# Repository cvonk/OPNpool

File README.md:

> OPNpool moved to a ESPHome/PlatformIO based build system.  If you are looking for the last standalone version, you will find that in the `standalone` branch, or download the most recent `v1` release.

Ever dreamed of making your pool smarter and easier to manage? If you’ve ever owned a backyard pool, you know it’s not just about swimming—there’s a whole world of chemicals, covers, vacuums, brushes, and fiddling with thermostats and circuits. Even with a saltwater pool, you’ve got to keep a close eye on things!

Enter OPNpool: your pool’s new best friend. It takes all the classic pool controller features and brings them into your smart home. OPNpool keeps track of your controller, pump, and chlorinator, so you don’t have to run outside every time you want to check or change something. Even better, you can set up automations—like running the pump longer when it’s hot out—all from the comfort of your phone or smart home dashboard.

Thanks to some clever folks who reverse engineered the RS485 protocol, OPNpool can eavesdrop on the chatter between your pool’s components. The ESP32 inside shares all that state info with Home Assistant.

# OPNpool

OPNpool is an open-source hardware and software solution that brings advanced pool automation to your smart home. By bridging legacy pool controllers with modern IoT platforms, OPNpool enables real-time monitoring, remote control, and seamless integration with Home Assistant. Whether you want to automate your pool pump based on temperature, monitor chlorinator status, or simply enjoy the convenience of remote access, OPNpool provides a robust and extensible platform for pool management.

## How it works

At its core, OPNpool connects an ESP32 microcontroller to your pool controller’s RS-485 bus. The ESP32 runs ESPHome firmware, which translates pool equipment data into Home Assistant entities. This allows you to view and control your pool’s thermostats, pumps, circuits, and chlorinator directly from your smart home dashboard or mobile app. The system is designed for reliability, safety, and ease of installation, with support for over-the-air updates and waterproof enclosures for outdoor use.

## Features

- [x] **Smart Home Integration:** Native support for Home Assistant and ESPHome.
- [x] **Remote Monitoring & Control:** Access your pool’s status and controls from anywhere.
- [x] **Community Driven:** Built on the work of pool automation enthusiasts and reverse engineers.
- [x] **Open Source:** Fully transparent hardware and software—customize and extend as needed.

## Getting started

No prior experience with pool automation or ESPHome is required. The documentation below will guide you through hardware assembly, wiring, firmware installation, and Home Assistant integration. If you have questions or need help, join the project’s GitHub Discussions for community support.

This device was tested with the Pentair SunTouch controller with firmware **2.080** (2013-07-15), connected to an IntelliFlo pump and IntelliChlor saltwater chlorinator.

> This open source and hardware project is intended to comply with the October 2016 exemption to the Digital Millennium Copyright Act allowing "good-faith" testing," in a controlled environment designed to avoid any harm to individuals or to the public.

## Acknowledgements

> We proudly acknowledge the work of reverse engineering pioneers [Joshua Bloch](https://docs.google.com/document/d/1M0KMfXfvbszKeqzu6MUF_7yM6KDHk8cZ5nrH1_OUcAc/edit), [Michael Russe](http://cocoontech.com/forums/files/file/173-pab014sharezip/), and [George Saw](http://cocoontech.com/forums/topic/27864-download-pitzip/). (Drop me a line if I forgot you.)

## Usage

Start with [installing the ESPHome environment](https://esphome.io/guides/installing_esphome/) on a beefy computer. In my case, this cut the compilation time to a minute, compared to half an hour when running it as an add-on to Home Assistant.

In an empty directory, create a `opnpool-1.yaml` configuration file as shown below.
```yaml
substitutions:
  device_name: opnpool-1
  friendly_name: "OPNpool meets ESPHome"
  description: "External component, see https://github.com/cvonk/OPNpool_meets_ESPHome"

esphome:
  name: ${device_name}
  comment: ${description}
  friendly_name: ${friendly_name}

esp32:
  variant: esp32c6          # or esp32     for <= r3 boards
  board: esp32-c6-devkitc-1 # or lolin_d32 for <= r3 boards
  framework:
    type: esp-idf

wifi:
  domain: !secret domain_name # only needed if not on the same subnet
  min_auth_mode: WPA2
  reboot_timeout: 0s
  networks:
  - ssid: !secret wifi_ssid
    password: !secret wifi_password

api:

ota:
  - platform: esphome
    password: !secret ota_password

external_components:
  - source: github://cvonk/OPNpool
    components: [ opnpool ]

logger:
  level: VERBOSE          # build includes ESP_LOGx up to VERBOSE
  initial_level: WARN     # only show up to WARN globally
  logs:
    poolstate_rx: VERBOSE # show decoded messages

opnpool:
  id: opnpool_1
  RS-485:
    tx_pin:  21  # or 26 for <= r3 boards 
    rx_pin:  22  # or 25 for <= r3 boards
    rts_pin: 23  # or 27 for <= r3 boards
```

Specify your own secrets in `secrets.yaml`

```yaml
wifi_ssid: "REDACTED"
wifi_password: "REDACTED"
domain_name: ".iot.example.com" # appended to base fname to create FQDN for OTA updates
ota_password: "REDACTED"
api_encryption_key: "REDACTED"
```

Compile and upload the code using

```bash
esphome run opnpool-1.yaml
```

The first time, you need to upload over USB Serial, but after that you can use over-the-air updates.

In the output, you should see something like:

```text
[16:26:54.983]I (423) boot: Loaded app from partition at offset 0x10000
[16:26:55.024]I (465) boot: Set actual ota_seq=1 in otadata[0]
[16:26:55.029]I (465) boot: Disabling RNG early entropy source...
[16:26:55.268][W][component:333]: api set Warning flag: unspecified
[16:26:55.273][W][component:342]: wifi set Warning flag: scanning for networks
[16:27:01.293][W][component:373]: wifi cleared Warning flag
[16:27:25.143][E][RS-485:108][pool_req_task]: tx_q full
[16:27:55.144][E][RS-485:108][pool_req_task]: tx_q full
```

In the above trace, the `tx_q full` indicates that it can't transmit to the pool controller.

If you haven't already, add the ESPHome integration to Home Assistant.

Under Integrations, you will find now notice that Home Assistant auto discovered your new device.

{: style="display: block; margin-left: auto; margin-right: auto; width:300px;}

Add it, and specify your API key.  Name the device and assign it an area. You should then see the enities although their values are `unknown`.  Time to populate those entities by connecting it to the pool controller ;-)

## Connect

At the core this project is an ESP32 module and a 3.3 Volt RS-485 adapter. You can
breadboard this using:

* Any ESP32 module that has an USB connector and three GPIO pins available.
* Any "Max485 Module TTL". To make it 3.3 Volt compliant, change the chip to a `MAX3485CSA+`. While you're at it, you may as well remove the 10 kΩ pullup resistors (typically labeled `R1` to `R4`).
* A piece of Cat5 ethernet cable to connect to the pool controller.

{: style="display: block; margin-left: auto; margin-right: auto; width:300px;}

If you prefer to make this a more permanent solution, I suggest rolling a printed circuit board and housing it in a IP68 waterproof case with IP68 connectors.  More about this later.

> :warning: **THIS PROJECT IS OFFERED AS IS. IF YOU USE IT YOU ASSUME ALL RISKS. NO WARRANTIES. At the very least, turn off the power while you work on your pool equipment. Be careful, THERE IS ALWAYS A RISK OF BREAKING YOUR POOL EQUIPMENT.**

Understanding the above warning .. the RS-485 header can be found on the back of the control board. There are probably already wires connected that go to the devices such as pump and chlorinator.

{: style="display: block; margin-left: auto; margin-right: auto; width:400px;}

To minimize electromagnetic interference, use a twisted pairs from e.g. CAT-5 cable to connect the `A`/`B` pair to the RS-485 adapter as shown in the table below.

| Controller       | RS-485 adapter | idle state |         
|:-----------------|:--------------:|:-----------|
| `-DATA` (green)  |  `A`           | negative   |
| `+DATA` (yellow) |  `B`           | positive   |

Connect the RS-485 adapter to the ESP32 module.  I also pulled `GPIO#27` down with a 10 k&ohm; resistor, to keep it from transmiting while the ESP32 is booting.

| RS-485 adapter | ESP32 module |
|:---------------|:-------------|
| RO             | `GPIO#25`    |
| DI             | `GPIO#26`    |
| DE and RE      | `GPIO#27`    |
| GND            | `GND`        |

The serial monitor will start to show decoded messages such as:

```json
{CTRL_VERSION_REQ: {}}
{CTRL_VERSION_RESP: {"firmware":"2.80"}}
{CTRL_TIME_REQ: {}}
{CTRL_TIME_RESP: {"tod":{"time":"18:51","date":"2026-01-18"}}}
{CTRL_HEAT_REQ: {}}
{CTRL_HEAT_RESP: {"thermos":{"POOL":{"temp":54,"sp":63,"src":"NONE"},"SPA":{"temp":54,"sp"}
```

> :bulb: If you don't see such messages, make sure you didn't swap the data leads, or oddly enough some people report that they do need to swap the data leads.  To debug the datalink framing, set the `datalink_rx` logger level to `VERBOSE` and build and upload the code again. See futher below.

In Home Assistant the entities should populate, and show on your favorite Lovelace UI.

{: style="display: block; margin-left: auto; margin-right: auto; width:500px}

## PCB

For a robust and weatherproof installation, we recommend building a custom printed circuit board (PCB) to house the ESP32-C6 module, RS-485 adapter, and DC/DC converter. This approach ensures reliable connections, easier mounting, and long-term durability—especially for outdoor or poolside environments.

{: style="display: block; margin-left: auto; margin-right: auto; width:500px}

Note that the photo above is from a rev 1 board.

### Schematic

The hardware design features a buck converter that supplies 5V to the `5V0` pin on the ESP32-C6 DevKitC-1-N8 daughterboard. The scotty diode prevent issues when the board is also powered via USB.

The main data path runs between the RS-485 connector and the ESP32-C6 on the DevKitC-1-N8. An optional termination resistor is included to minimize signal reflections on the RS-485 bus.

### Board Layout

The entire schematic fits comfortably on a compact two-layer PCB. The board was designed using the free version of AutoDesk EAGLE, and all source files — including layout and schematics — are available in the [hardware directory](tree/main/hardware) of this repository.

{: style="display: block; margin-left: auto; margin-right: auto;}

### Bill of materials

| Name        | Description                                              | Suggested mfr/part#        | Price paid
|-------------|----------------------------------------------------------|----------------------------|-----------
| PBC r4      | Printed circuit board                                    | OSHPark                    | [$9.43](https://oshpark.com/)
| Enclosure   | 158x90x60mm ABS Plastic Junction Box, IP65               | *white label*              | [$9.81](https://www.harfington.com/products/p-1159792)
| RS-485_CONN | 5P Plug+socket, 5-pin, 16mm aviation, IP68               | SP16 5P                    | [$3.98](https://www.aliexpress.us/item/2251832722757291.html)
| RS-485-TERM | Fixed terminal block, 4-pin, screwless, 5 mm pitch       | Phoenix-Contact 1862437    | [$2.02](https://www.digikey.com/en/products/detail/phoenix-contact/1862437/6605421)
| ESP32-C6 DevKitC-1-N8 | ESP32-C6 dev board with 8MB flash, based on ESP32-C6-WROOM | ESP32-C6 DevKitC-1-N8      | [$9.00](https://www.digikey.com/en/products/detail/espressif-systems/ESP32-C6-DEVKITC-1-N8/17728861)
| MAX3485     | Maxim MAX3485CSA, RS-485/UART interface IC 3.3V, 8-SOIC  | Analog-Devices MAX3485CSA+T | [$5.64](https://www.digikey.com/en/products/detail/analog-devices-inc-maxim-integrated/MAX3485CSA-T/1703654)
| DC1         | DC/DC Converter R-78E5.0-0.5, 7-28V to 5V, 0.5A, 3-SIP   | RECOM-Power R-78E5.0-0.5   | [$3.30](https://www.digikey.com/en/products/detail/recom-power/R-78E5-0-0-5/2834904?s=N4IgTCBcDaIEoFEDCB5AsgWgAoHsDuApgE4AEcGA7ABwICsAdAAwaP20gC6AvkA)
| D1, D2      | Schottky Diode, 1N5818, 30V, 1A, DO-41                   | Diodes Incorporated 1N5818-T | [$0.30](https://www.digikey.com/en/products/detail/diodes-incorporated/1N5818-T/22054)
| LED1        | LED, Green Clear 571nm, 1206                             | Lite-On LTST-C150KGKT       | [$0.15](https://www.digikey.com/en/products/detail/liteon/LTST-C150KGKT/365085)
| LED2        | LED, Amber Clear 602nm, 1206                             | Lite-On LTST-C150AKT       | [$0.15](https://www.digikey.com/en/products/detail/liteon/LTST-C150AKT/269213)
| C1, C2      | Capacitor, 10 µF, 25 V, multi-layer ceramic, 0805        | KEMET C0805C106K3PACTU     | [$0.22](https://www.digikey.com/en/products/detail/kemet/C0805C106K3PACTU/5267604?s=N4IgTCBcDaINIFECyCAqACAwgBgBzYFZMBGbANjgGYAFAQU1QFUQBdAXyA)
| C3          | Capacitor, 100 nF, 25 V, multi-layer ceramic, 0805      | KEMET C0805C104M3RACTU     | [$0.12](https://www.digikey.com/en/products/detail/kemet/C0805C104M3RACTU/2211748?s=N4IgTCBcDaINIFECyCAqACAwgBgBzYFZMBGbAFiQGYAlAQU1QFUQBdAXyA)
| R1, R2      | Resistor, 68 Ω, 1/8 W, 0805                              | YAGEO RC0805FR-0768RL      | [$0.20](https://www.digikey.com/en/products/detail/yageo/RC0805FR-0768RL/728097?s=N4IgTCBcDaIJoEEDiBRA8gAgEoGEAMAHHgKwBiWAtHgOwBsBWAMiALoC%2BQA)
| R3          | Not stuffed, resistor, 120 Ω, 1/4 W, 0805                | KAO SG73S2ATTD121J         | [$0.00](https://www.digikey.com/en/products/detail/koa-speer-electronics-inc/RK73B2ATTD121J/10236600)
| PCB Screws  | Machine screw, #6-32 x x 3/16", panhead                  | Keystone-Electronics 9306  | [$0.10](https://www.digikey.com/en/products/detail/keystone-electronics/9306/2746085?s=N4IgjCBcpgTB0QGMoDMCGAbAzgUwDQgD2UA2iLAAwCsIAuoQA4AuUIAyswE4CWAdgHMQAX2GFYZEAGlcAT2zMifXAFoAoplxJuSnkmwACAJwBmSgDZ6woA)
| CONN Screws | Machine screw, M2-0.4 x 16 mm, cheese head               | Essentra 50M020040D016     | [$0.28](https://www.digikey.com/en/products/detail/essentra-components/50M020040D016/11639297)
| CONN Nuts   | Hex nut, M2-0.4, nylon                                   | Essentra 04M020040HN       | [$0.15](https://www.digikey.com/en/products/detail/essentra-components/04M020040HN/9677098)

Note that tariffs and shipping will add to the cost.

## Troubleshooting

Not all controller firmwares are created equally.  If you are not using firmware version 2.080, you will need dive down to the byte level and to tweak the network layer.  If you succeed, please send me an pull request, and I will iinclude it in the next release.

To show more (or less) debug information, specify the levels in `opnpoool-1.yaml`

```yaml
logger:
  level: VERBOSE       # build includes ESP_LOGx up to VERBOSE
  initial_level: WARN  # only show up to WARN globally
  logs:
    rs485: WARN
    datalink_rx: WARN
    datalink_tx: WARN
    network_rx: WARN
    network_create: WARN
    pool_task: WARN
    ipc: WARN
    poolstate: WARN
    poolstate_rx: VERBOSE
    opnpool: WARN
    opnpool_climate: WARN
    opnpool_switch: WARN
    opnpool_sensor: WARN
    opnpool_binary_sensor: WARN
    opnpool_text_sensor: WARN
    enum_helpers: WARN
```

For the `logger` component, it is recommended to use the following levels: `WARN`, which shows only warnings and errors; `INFO`, which includes informational messages such as configuration details, warnings, and errors; and `VERBOSE`, which provides very detailed logs, info, warnings, and errors. Be careful not to enable too much logging, as excessive output can negatively impact the connection between Home Assistant and the ESP32-C6.

### Decoding Stack Traces

If your ESP32-C6 crashes and you notice stack traces in the serial log, you can simplify debugging by enabling ESPHome's stack trace decoder. With this feature, exception addresses are automatically translated into human-readable function names and line numbers within your logs.

To activate the stack trace decoder, add the following lines to your YAML configuration:

```yaml
debug:
  update_interval: 5s  # for exception decoding in logs
```

> **Tip:** Detailed crash information will only appear on the serial console (not in the web logs). Be sure to check the serial output for troubleshooting.

# FAQ

**LEDs not blinking with RS-485 connected**

If communication fails, swap the `-DATA` and `+DATA` wires, as standards for these labels vary. 

**Is a controller required?**

This setup ensures that when selling the house, the next owner is not stuck with a "custom" system. They can use the pool conventionally or easily adopt the smart features.  If you're determined to build your own controller, I can recommend Russ Goldin's [nodejs-poolController](https://github.com/tagyoureit/nodejs-poolController/tree/master).

**Will it work with ___ board?**

There are many boards and kits that incorporate the ESP32. I started with the ESP8266, switched to the original ESP32, and use the ESP-C6. At this point it probably runs on any ESP32 flavor board. If you want to try something else, sure feel free the code is written to be portable. Just make sure you use the MAX3485 instead of the TTL-level MAX485.

**My firmware is ___ How do you update SunTouch firmware?**

Instead of taking such a risky step, I recommend enabling `VERBOSE` logging for `datalink_rx` and `network_rx`.  This will visualize the raw bytes received and messages interpretated. Compare that with the structures `network_msg.h`, and update the file as needed.

> Only do this if you very confident with flashing electronics. You risk bricking your pool controller.

Having read the above warning, you can upgrade if your controller is at [version 2.x](https://saturationregion.blogspot.com/2020/01/whats-deal-with-easytouch-versions-1.html). You will need to get a [USBDM JS16](https://www.aliexpress.us/w/wholesale-Freescale-USBDM-Programmer-JS16.html?spm=a2g0o.detail.search.0) programmer, [make](https://www.troublefreepool.com/threads/how-to-perform-firmware-upgrade-on-pentair-controllers.69589/#post-595657) a [JST cable](https://www.aliexpress.us/w/wholesale-5-PCS-JST-1.-25mm-Male-Female-6p.html?spm=a2g0o.detail.search.0) following [the instructions](https://www.troublefreepool.com/threads/how-to-perform-firmware-upgrade-on-pentair-controllers.69589/page-7#post-2021911).

#
I hope this project brings you joy.  Keep in touch through the dicussion forum.

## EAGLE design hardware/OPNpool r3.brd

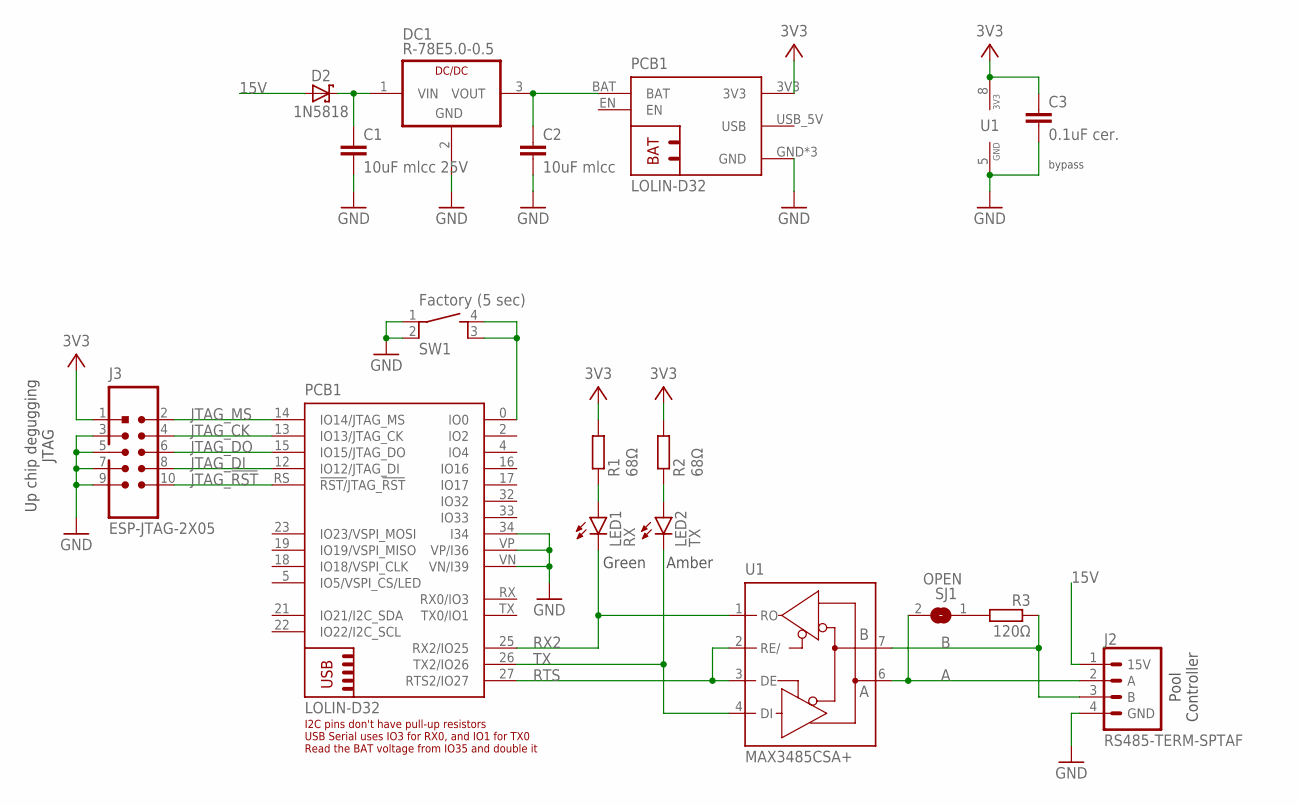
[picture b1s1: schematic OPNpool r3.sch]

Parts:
C1: 10uF mlcc 25V; C0805K; MOUSER# 81-GJ821BR61E106KE1L
C2: 10uF mlcc; C0805K; MOUSER# 81-GJ821BR61E106KE1L
C3: 0.1uF cer.; C0805K; MOUSER# 80-C0805C104K1REAUTO
D2: 1N5818; DO41-7.6; MOUSER# 583-1N5818-T
DC1: R-78E5.0-0.5; SIP3; MOUSER# 919-R-78E5.0-0.5
J2: RS485-TERM-SPTAF; SPTAF1/4-5,0-LL; MOUSER# 651-1864451
J3: ESP-JTAG-2X05; 2X05_SHROUDED; MOUSER# 538-70246-1004; DIGIKEY# WM3478-ND
LED1: RX; CHIPLED_0805
LED2: TX; CHIPLED_0805
PCB1: LOLIN-D32
R1, R2: 68Ω; R0805; MOUSER# 652-CRM0805JW1R5ELF
R3: 120Ω; R0805; MOUSER# 652-CRM0805JW1R5ELF
SJ1: OPEN; SJ
SW1: Factory (5 sec); TE_1-1825910-4
U1: MAX3485CSA+; SO08; MOUSER# 700-MAX3485CSA

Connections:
3V3: C3.1, J3.1 (3V3), PCB1.3V3, R1.2, R2.2, U1.8 (VCC)
15V: D2.A, J2.1 (15V)
A: J2.2 (A), SJ1.2, U1.6 (A)
B: J2.3 (B), R3.1, U1.7 (B)
GND: C1.2, C2.2, C3.2, DC1.2 (GND), J2.4 (GND), J3.3 (GND), J3.5 (GND), J3.7 (GND), J3.9 (GND), PCB1.34 (I34), PCB1.GND, PCB1.GND@1 (GND), PCB1.GND@2 (GND), PCB1.VN (VN/I39), PCB1.VP (VP/I36), SW1.1, SW1.2, U1.5 (GND)
JTAG_!RST: J3.10 (NC), PCB1.RS (!RST/!JTAG_!RST)
JTAG_CK: J3.4 (TCK), PCB1.13 (IO13/JTAG_CK)
JTAG_DI: J3.8 (TDI), PCB1.12 (IO12/JTAG_DI)
JTAG_DO: J3.6 (TDO), PCB1.15 (IO15/JTAG_DO)
JTAG_MS: J3.2 (TMS), PCB1.14 (IO14/JTAG_MS)
unnamed: LED1.A, R1.1
unnamed: LED2.A, R2.1
unnamed: PCB1.0 (IO0), SW1.3, SW1.4
unnamed: R3.2, SJ1.1
RTS: PCB1.27 (RTS2/IO27), U1.2 (RE/), U1.3 (DE)
RX2: LED1.C, PCB1.25 (RX2/IO25), U1.1 (RO)
TX: LED2.C, PCB1.26 (TX2/IO26), U1.4 (DI)
VIN: C1.1, D2.C, DC1.1 (VIN)
VOUT: C2.1, DC1.3 (VOUT), PCB1.BAT

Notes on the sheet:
Up chip degugging JTAG
Pool Controller
bypass
Green
Amber

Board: 2 copper layers, 16 parts (0 on the bottom side), 19 nets, no tracks yet.

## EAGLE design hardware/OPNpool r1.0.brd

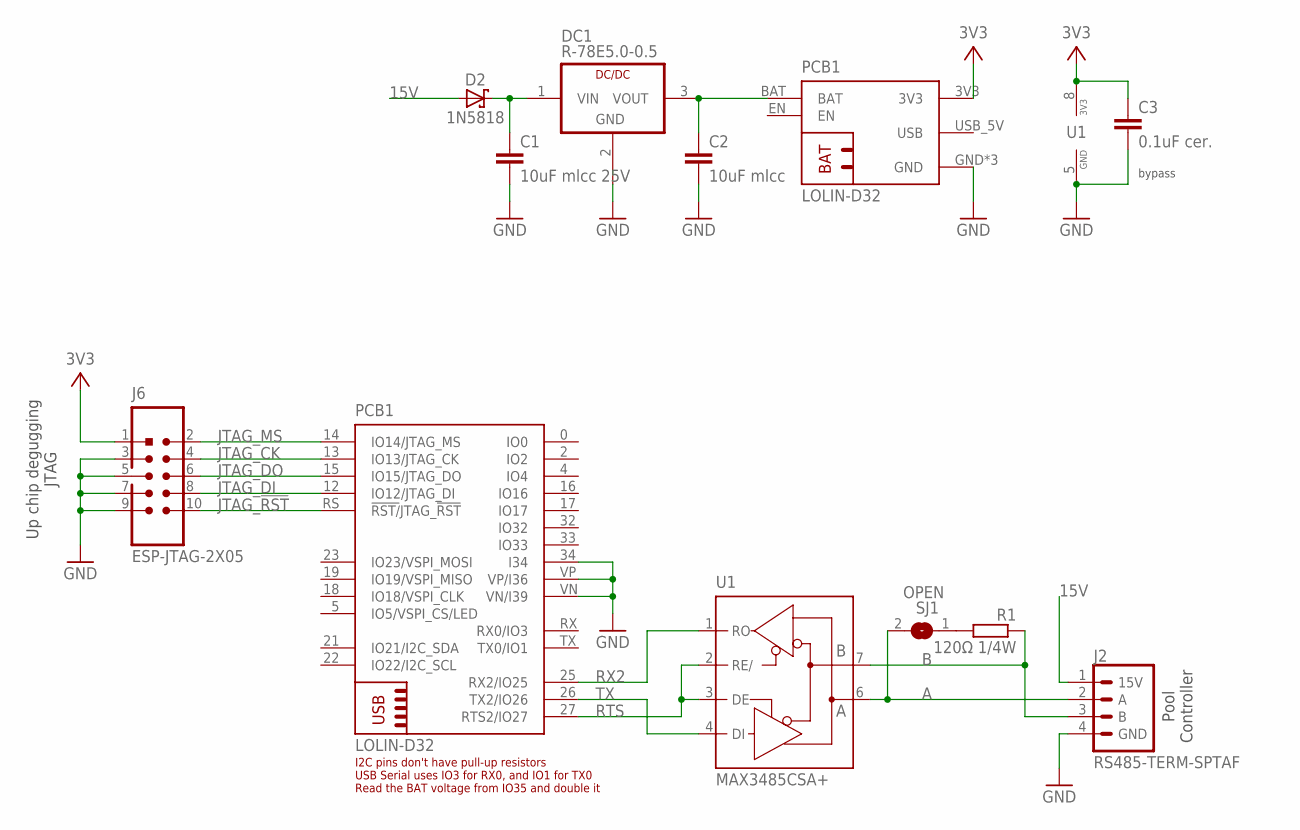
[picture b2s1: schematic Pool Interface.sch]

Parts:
C1: 10uF mlcc 25V; C0805K; MOUSER# 81-GJ821BR61E106KE1L
C2: 10uF mlcc; C0805K; MOUSER# 81-GJ821BR61E106KE1L
C3: 0.1uF cer.; C0805K; MOUSER# 80-C0805C104K1REAUTO
D2: 1N5818; DO41-7.6; MOUSER# 583-1N5818-T
DC1: R-78E5.0-0.5; SIP3; MOUSER# 919-R-78E5.0-0.5
J2: RS485-TERM-SPTAF; SPTAF1/4-5,0-LL; MOUSER# 651-1864451
J6: ESP-JTAG-2X05; 2X05_SHROUDED; MOUSER# 538-70246-1004; DIGIKEY# WM3478-ND
PCB1: LOLIN-D32
R1: 120Ω 1/4W; R0805; MOUSER# 652-CRM0805JW1R5ELF
SJ1: OPEN; SJ
U1: MAX3485CSA+; SO08; MOUSER# 700-MAX3485CSA

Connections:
3V3: C3.1, J6.1 (3V3), PCB1.3V3, U1.8 (VCC)
15V: D2.A, J2.1 (15V)
A: J2.2 (A), SJ1.2, U1.6 (A)
B: J2.3 (B), R1.1, U1.7 (B)
GND: C1.2, C2.2, C3.2, DC1.2 (GND), J2.4 (GND), J6.3 (GND), J6.5 (GND), J6.7 (GND), J6.9 (GND), PCB1.34 (I34), PCB1.GND, PCB1.GND@1 (GND), PCB1.GND@2 (GND), PCB1.VN (VN/I39), PCB1.VP (VP/I36), U1.5 (GND)
JTAG_!RST: J6.10 (NC), PCB1.RS (!RST/!JTAG_!RST)
JTAG_CK: J6.4 (TCK), PCB1.13 (IO13/JTAG_CK)
JTAG_DI: J6.8 (TDI), PCB1.12 (IO12/JTAG_DI)
JTAG_DO: J6.6 (TDO), PCB1.15 (IO15/JTAG_DO)
JTAG_MS: J6.2 (TMS), PCB1.14 (IO14/JTAG_MS)
unnamed: R1.2, SJ1.1
RTS: PCB1.27 (RTS2/IO27), U1.2 (RE/), U1.3 (DE)
RX2: PCB1.25 (RX2/IO25), U1.1 (RO)
TX: PCB1.26 (TX2/IO26), U1.4 (DI)
VIN: C1.1, D2.C, DC1.1 (VIN)
VOUT: C2.1, DC1.3 (VOUT), PCB1.BAT

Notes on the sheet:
Up chip degugging JTAG
Pool Controller
bypass

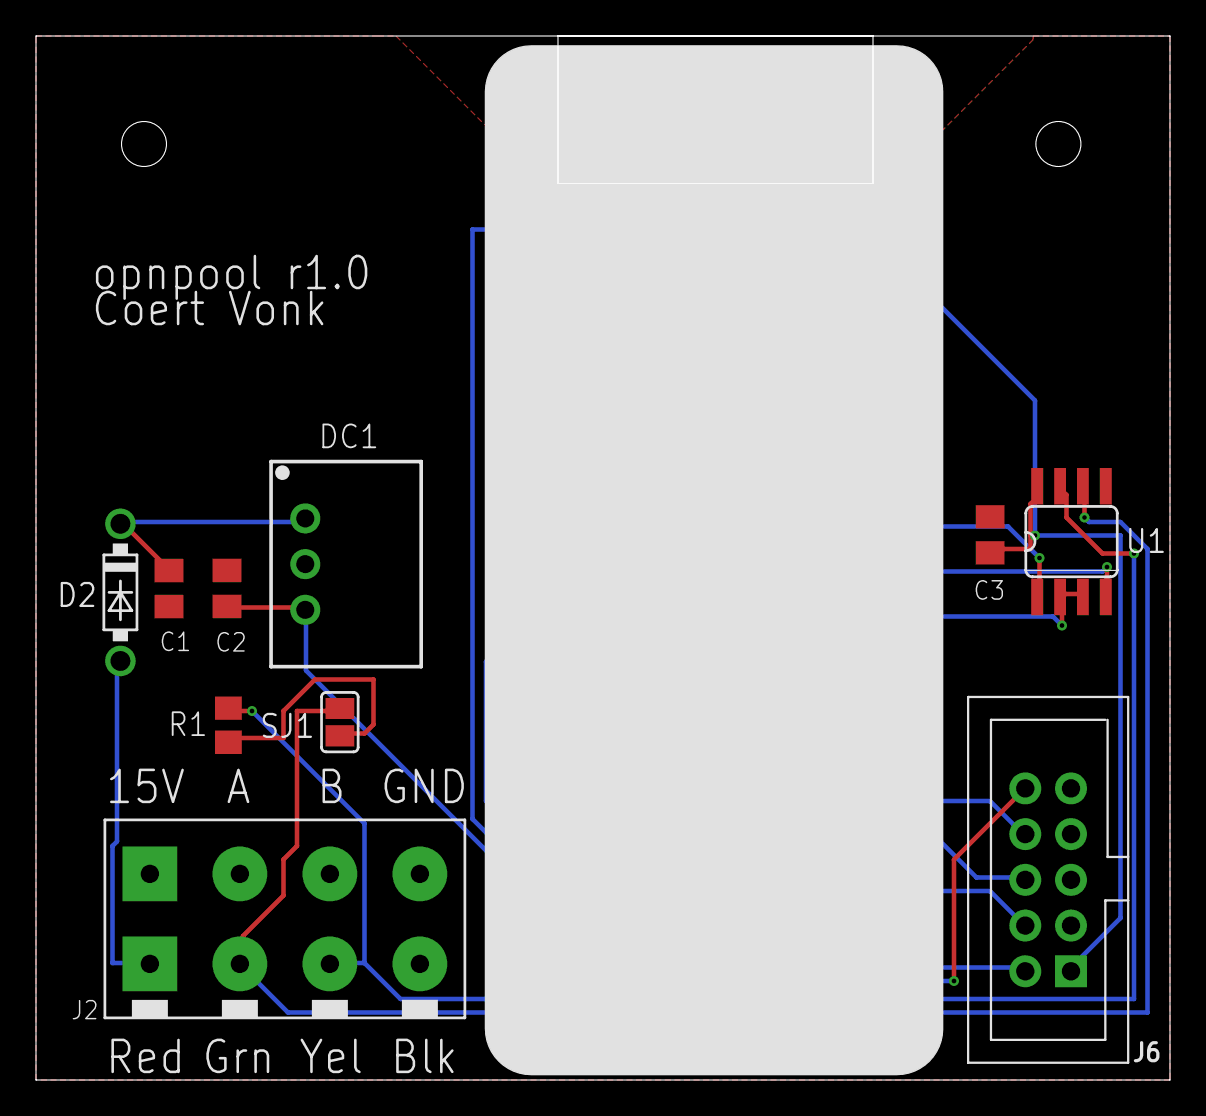
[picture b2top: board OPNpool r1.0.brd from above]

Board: 2 copper layers, 63.0 x 58.0 mm, 11 parts (0 on the bottom side), 16 nets.

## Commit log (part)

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2022-03-13 change comment
2022-03-13 rename IPC_TO_MQTT_TYP_*
2022-03-15 add illustrations for design docs
2022-03-15 rename webapp to webai; bug fixes; traces
2022-03-15 add httpd for /who; add circuit_topic to climate
2022-03-16 Add font used in AI illustrations
2022-03-16 Add mDNS
2022-03-17 Only register active schedules
2022-03-19 add hass binary_sensor
2022-03-19 correct hass entitys
2022-03-19 change order of _dispatches[]
2022-03-21 new sched reporting; fix switch value; add if_vers
2022-03-26 Sending MQTT URL across
2022-03-26 Added wait for MQTT/OTA/Reboot in #if 0
2022-03-26 store mqtt_url in nvram; don't pass 0 temp
2022-03-28 rm old
2022-03-28 Removed submodule
2022-03-28 added Android provisioning
2022-03-29 add few more proto details
2022-03-29 update android submodule
2022-03-29 fix compile err
2022-03-29 add releases
2022-03-29 update android to master
2022-03-30 add screenshots and android binaries
2022-03-30 add ble prov mqtt-status and ota-update endpoints
2022-03-30 use opnpool in mDNS
2022-03-30 add new release (rm old)
2022-03-30 add android releases (and rm old ones)
2022-03-31 Make visibility depend on state
2022-03-31 fix err in thermostat src (in Web UI)
2022-03-31 add released binaries
2022-03-31 bump android
2022-03-31 change com port
2022-03-31 pulled android in
2022-03-31 rm unneeded srs
2022-03-31 rename
2022-03-31 add fact reset to factory; rename
2022-03-31 rm binary
2022-03-31 add binaries; fix web UI
2022-03-31 add android binaries
2022-04-02 add design docs
2022-04-02 update design imgs
2022-04-02 update design doc
2022-04-02 update hardware design doc
2022-04-02 add hardware design imgs
2022-04-02 refresh imgs
2022-04-02 add hardware assembly video
2022-04-02 change white balance
2022-04-02 add pcb to releases
2022-04-02 add lib
2022-04-02 rm order info
2022-04-02 split schematic
2022-04-03 change name for hassio
2022-04-04 No OTA when interface runs from factory partition.
2022-04-04 Update submodule
2022-04-04 strip images
2022-04-04 crop
2022-04-04 update web ui
2022-04-04 add icon
2022-04-04 add svg
2022-04-04 add imgs
2022-04-04 combine and split
2022-04-04 compress
2022-04-05 add yaml
2022-04-05 tweak imgs
2022-04-05 update ota_update_task submodule
2022-04-05 update docs
2022-04-05 updaet docs
2022-04-05 update img
2022-04-05 pull in android changes
2022-04-06 Allow hardcoded WiFi credentials
2022-04-06 pull in submodule changes
2022-04-06 allow empty mqtt url
2022-04-06 add README release bin
2022-04-06 change name to OPNpool
2022-04-06 update doc
2022-04-07 Create LICENSE
2022-04-07 update license
2022-04-07 mv hardware files
2022-04-07 rm settings.json from git
2022-04-07 exclude .vscode/
2022-04-07 don't use travis
2022-04-07 rm outdated url
2022-04-07 cleanup research notes and refs
2022-04-07 cleanup research
2022-04-07 moe media files
2022-04-07 mv media to assets folder
2022-04-07 mv folder
2022-04-07 add links to design doc
2022-04-07 help intelisense
2022-04-07 Removed submodules
2022-04-07 move design / research docs to OPNpool_design prj
2022-04-08 ignore EagleCAD tmp files
2022-04-08 Respin board
2022-04-08 add block schematics
2022-04-08 redo video with light theme
2022-04-09 add releases; corr spelling
2022-04-10 update url
2022-04-10 update port
2022-04-10 change URL for android submodule
2022-04-10 pull in android update
2022-04-10 pull in changes
2022-04-11 correct legal
2022-04-11 move imgs/vids around
2022-04-12 add esp32-wroom32 eagle lib
2022-04-13 add inside pool ctrl view
2022-04-13 update mqtt details
2022-04-13 spelling
2022-04-14 released android
2022-04-14 add graphics
2022-04-14 release some of the design chapters
2022-04-14 pull in android updates
2022-04-14 fix json string
2022-04-14 rename brd/sch
2022-04-14 add comment about extra units
2022-04-15 add resized imgs
2022-04-15 don't configure cmake on open
2022-04-17 correct spelling
2022-04-18 Release remaining design docs
2022-04-20 switch to master for submodules
2022-04-20 corr spell
2022-04-28 correct path
2022-04-28 add comment
2022-04-28 fix #define
2022-04-28 bump submodule version
2022-05-03 change screw holes; invert LEDs
2022-05-04 add SPDX id
2022-05-13 routed pcb r3
2023-08-14 Fixed dangling pointer to config. @bishopdynamics
2023-08-14 Fix MQTT Discovery for Home Assistant 2023.8.2
2023-08-14 prevent compiler warning
2024-01-23 Update README.md
    Include command to add mDNS component.
2024-12-30 Fix git submodule url
2024-12-30 fix git module factory url and directory
2025-07-23 Update FULL_INSTALL.md
    App pulled from G play store. Is available through the Releases tab instead.
2026-01-07 prevent *(random) read, by change network_msg_t to have a bytes[0] member instead of *bytes.
2026-01-07 add doxygen blocks
2026-01-07 Resolve the squiggles under included esp headers
2026-01-07 fix skb_pull()
2026-01-20 Update README with OPNpool meets ESPHome link
    Added a link to the new spinoff project OPNpool meets ESPHome.
2026-01-20 Clarify release note for OPNpool meets ESPHome
    Updated the README to clarify the release of OPNpool meets ESPHome for Home Assistant users.
2026-01-20 Highlight OPNpool meets ESPHome release
    Updated README to emphasize the release of OPNpool meets ESPHome.
2026-01-20 Enhance README with new project information
    Updated README to include additional details about OPNpool meets ESPHome.
2026-02-11 prepare for move to OPNHome platform
2026-02-11 prepare for move to OPNHome platform #3
2026-02-11 Move to ESPHome/PlatformIO based build system.
2026-02-11 New features:
    Add native Home Assistant support by using ESPHome/PlatformIO build
    system.
    Add support for Thread network transport, in preparation for
    Matter/Thread.
    Switch to esp32-c6-devkitc-1 module for Matter/Thread support.
    Learns the controller address from its broadcast.
2026-02-12 migrate to KiCad
2026-02-18 move from Eagle to KiCad symbols
2026-02-19 Fix ERC errors
2026-02-19 reorg hardware dirs
2026-02-19 correct fnames
2026-02-19 bump rev
2026-06-02 Add air-temperature fix and solar1/solar2 temperature sensors
    Brings in the upstream air-temperature-sensor fix and dual solar-temperature
    sensors (solar1/solar2), reconciled so sensor_id_t, poolstate_temp_typ_t,
    CONF_ANALOG_SENSORS, and poolstate_rx stay consistent and the build is clean
    (SOLAR_1 from solar_temp_1, SOLAR_2 from solar_temp_2).
2026-06-03 pump rpm fix
2026-06-04 Make solar and pump-flow sensors opt-in
    solar1_temperature, solar2_temperature, and primary_pump_flow are now only
    created when explicitly listed in YAML (previously every analog sensor was
    force-created with a default name). Most systems have no solar sensors, and
    variable-speed pumps never report flow, so these showed up as useless 0/spurious
    entities. Their sensor_id_t slots still exist; codegen just skips binding them
    and the C++ already null-checks each sensor. Example opnpool-1.yaml comments them

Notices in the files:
README.md:
License: GPL v3
